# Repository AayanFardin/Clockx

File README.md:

# Clockx
ClockX is a custom-built digital clock powered by an ESP32-S3. It includes a 2.25-inch TFT display, physical control buttons, a rechargeable battery, a custom-designed PCB, and a 3D-printed enclosure.
# Functions
- Usual Time display
- Alarm
- Stopwatch
- Timer
- Custom rington option
- There are some holes for USB, Buzzer, Battery and display with tolerances of 0.5mm.

# Interesting Fact

- The alarm clock is soo tiny. Its like less then 110mm in all sides.
# Why I made this?
- So basically I go to my school often late and to make me wake up I made this clock.
- Moreover to help me in studies with the timer and stopwatch
- Also to give my table a cool look with my hand made stuffs
# CAD
Below, is my cad, made in Onshape

# Scematic and PCB Layout
Below, is my schematic and PCB layout, made in KiCad

# CLOCKX – Bill of Materials (BOM)

| No. | Component | Quantity | Status | Price (CAD) |
|---|---|---|---|---:|
| 1 | Cherry MX Switches | 4x | I can afford | — |
| 2 | DSA Keycaps | 4x | I can afford | — |
| 3 | [Seeed XIAO ESP32C3](https://www.aliexpress.com/item/1005006979844970.html) | 1x | Required | $6.15 |
| 4 | [2.25-inch TFT Screen](https://www.aliexpress.com/item/1005011855033572.html) | 1x | Required | $1.74 |
| 5 | 3.3V Piezo Buzzer | 1x | I can afford | — |
| 6 | 2.54mm 8-Pin Male Header | 1x | I can afford | — |
| 7 | 2.54mm 14-Pin Male-Female Header | 1x | I can afford | — |
| 8 | 20cm Female-Female Jumper Wires | 8x | I can afford | — |
| 9 | M3x5x4 Heatset Inserts | 8x | I can afford | — |
| 10 | M3x8mm Screws | 4x | I can afford | — |
| 11 | M3x16mm Screws | 4x | I can afford | — |
| 12 | 3D-Printed Case | 1x | Required (Price not sure) |  Required (Price not sure) |
| 13 | PCB(Including shipping) | 1x | Required | ~$10.36 |
| 14 | [18650 Battery Case](https://www.aliexpress.com/item/4001207701699.html) | 1x | Required | $3.46 |
| 15 | [18650 Batteries](https://www.aliexpress.com/item/1005007657633749.html) | 2x | Required | $9.89 |
| 16 | Buck Converter | 1x | I can afford | — |
|---|---|---|---|---:|
| | **Component Subtotal** | | | **$31.60** |
| | **Shipping for Components(not PCB)** | | | **$9.30** |
| | **TOTAL** | | | **$40.90 CAD** |

**Note:** The total includes only components and PCB with known prices and shipping. The 3D-printed case price are not included since am not sure.

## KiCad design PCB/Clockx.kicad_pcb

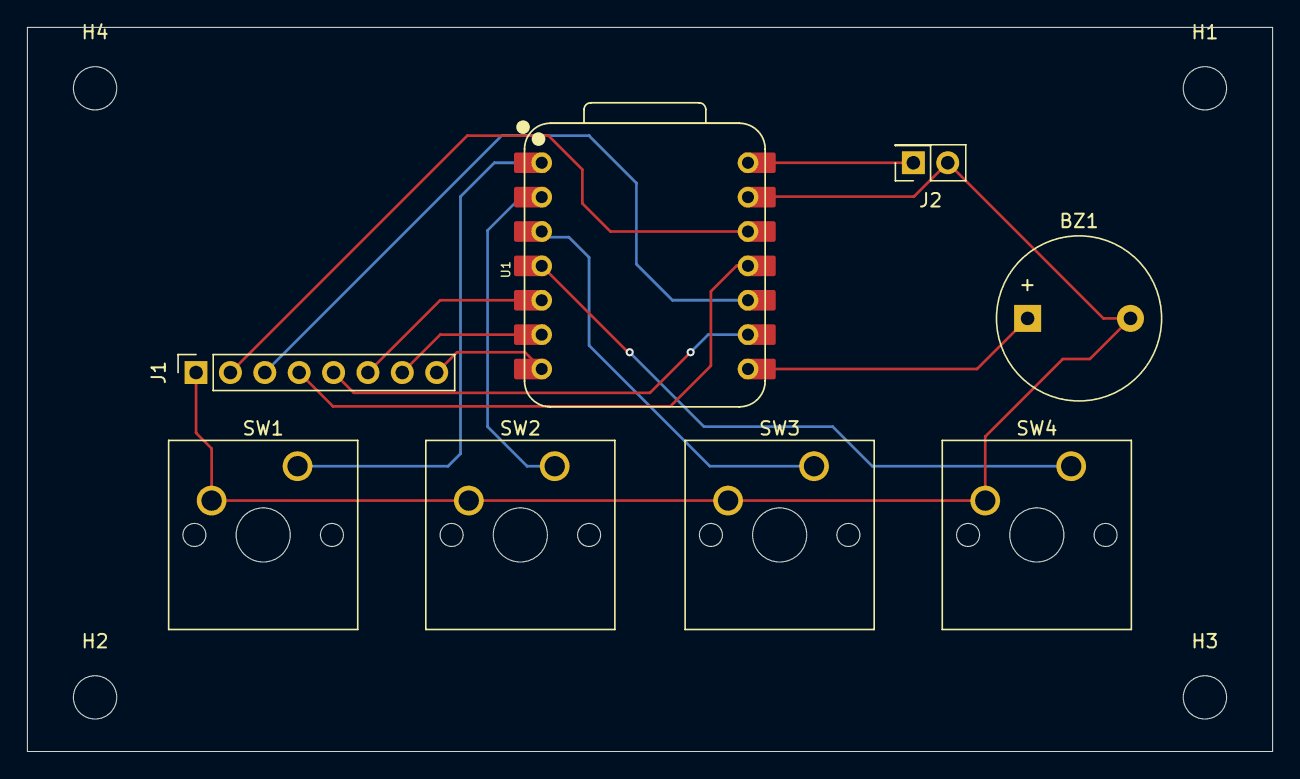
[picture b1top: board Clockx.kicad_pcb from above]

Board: 2 copper layers, 92.0 x 53.5 mm, 12 parts (0 on the bottom side), 14 nets.

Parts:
BZ1: Buzzer; Buzzer_12x9.5RM7.6
H1, H2, H3, H4: MountingHole; MountingHole_3.2mm_M3
J1: Conn_01x08_Pin; PinSocket_1x08_P2.54mm_Vertical
J2: 18650battery; PinSocket_2x01_P2.54mm_Vertical
SW1, SW2, SW3, SW4: SW_Push; SW_Cherry_MX_1.00u_PCB
U1: XIAO-ESP32-C3-SMD; XIAO-ESP32-C3-DIP

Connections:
/BL: J1.8, U1.7 (D6)
/CS: J1.7, U1.6 (D5)
/DC: J1.6, U1.5 (D4)
/RST: J1.5, U1.9 (D8)
/SCL: J1.3, U1.10 (D9/BOOT)
/SDA: J1.4, U1.11 (D10)
GND: BZ1.2 (-), J1.1, J2.2, SW1.2, SW2.2, SW3.2, SW4.2, U1.13 (GND)
unnamed: BZ1.1 (+), U1.8 (D7)
unnamed: J2.1, U1.14 (VBUS)
unnamed: SW1.1, U1.1 (D0)
unnamed: SW2.1, U1.2 (D1)
unnamed: SW3.1, U1.3 (D2)
unnamed: SW4.1, U1.4 (D3)
VCC: J1.2, U1.12 (3V3_OUT)
